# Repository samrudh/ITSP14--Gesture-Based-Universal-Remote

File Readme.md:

A summer project done in May-June 2014
| Gesture Based universal remote |

Description: It is a project aimed at 
implementing gesture based universal remote control of all the devices 
working with IR remote protocol.

Our wearable device first learns the IR codes, and mimic its functionality
when particular gesture is made.

Authors:
Ankit Patil,
Shubham Patil,
Sukhada Bakare

Mentor:
Samrudha Kelkar

Reference:
Arduino IR library
IRremote library for the Arduino.
For details on the library see the Wiki on github or the blog post http://arcfn.com/2009/08/multi-protocol-infrared-remote-library.html

Copyright 2009-2012 Ken Shirriff

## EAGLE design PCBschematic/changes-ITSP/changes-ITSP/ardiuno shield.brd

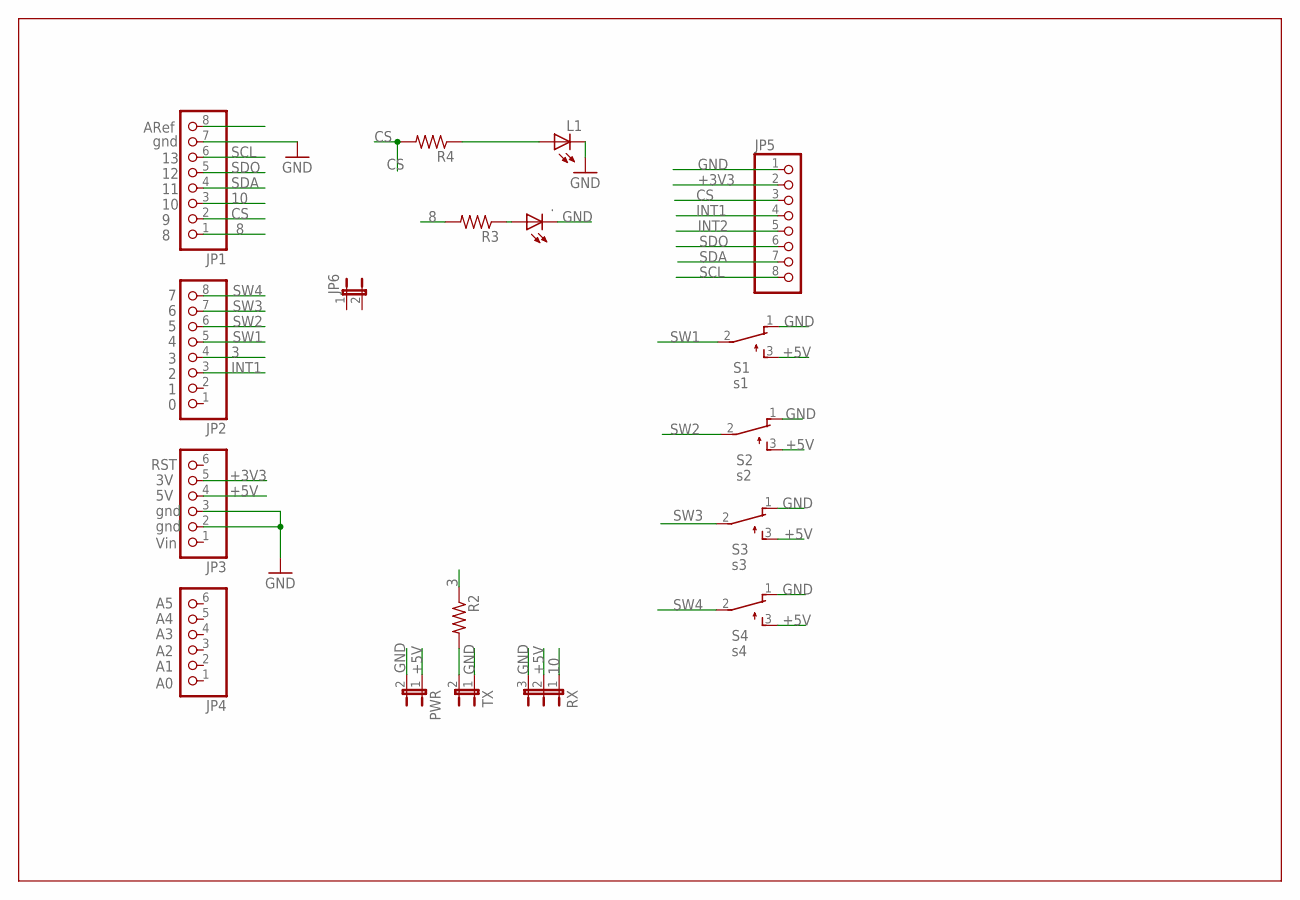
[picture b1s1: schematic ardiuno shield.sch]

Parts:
.: LED5MM
JP1, JP2, JP5: PINHD-1X8; 1X08
JP3, JP4: PINHD-1X6; 1X06
JP6: JP1E; JP1
L1: LED5MM
PWR: JP1E; JP1
R2, R3, R4: R-US_0207/10; 0207/10
RX: JP2E; JP2
S1: s1; TL3XPO
S2: s2; TL3XPO
S3: s3; TL3XPO
S4: s4; TL3XPO
TX: JP1E; JP1

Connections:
3: JP2.4, R2.1
8: JP1.1, R3.2
10: JP1.3, RX.1
+3V3: JP3.5, JP5.2
+5V: JP3.4, PWR.1, RX.2, S1.3 (S), S2.3 (S), S3.3 (S), S4.3 (S)
CS: JP1.2, JP5.3, R4.2
GND: ..K (C), JP1.7, JP3.2, JP3.3, JP5.1, L1.K (C), PWR.2, RX.3, S1.1 (O), S2.1 (O), S3.1 (O), S4.1 (O), TX.1
INT1: JP2.3, JP5.4
INT2: JP5.5
unnamed: L1.A, R4.1
unnamed: ..A, R3.1
unnamed: R2.2, TX.2
SCL: JP1.6, JP5.8
SDA: JP1.4, JP5.7
SDO: JP1.5, JP5.6
SW1: JP2.5, S1.2
SW2: JP2.6, S2.2
SW3: JP2.7, S3.2
SW4: JP2.8, S4.2

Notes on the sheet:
gnd
ARef
Vin
RST

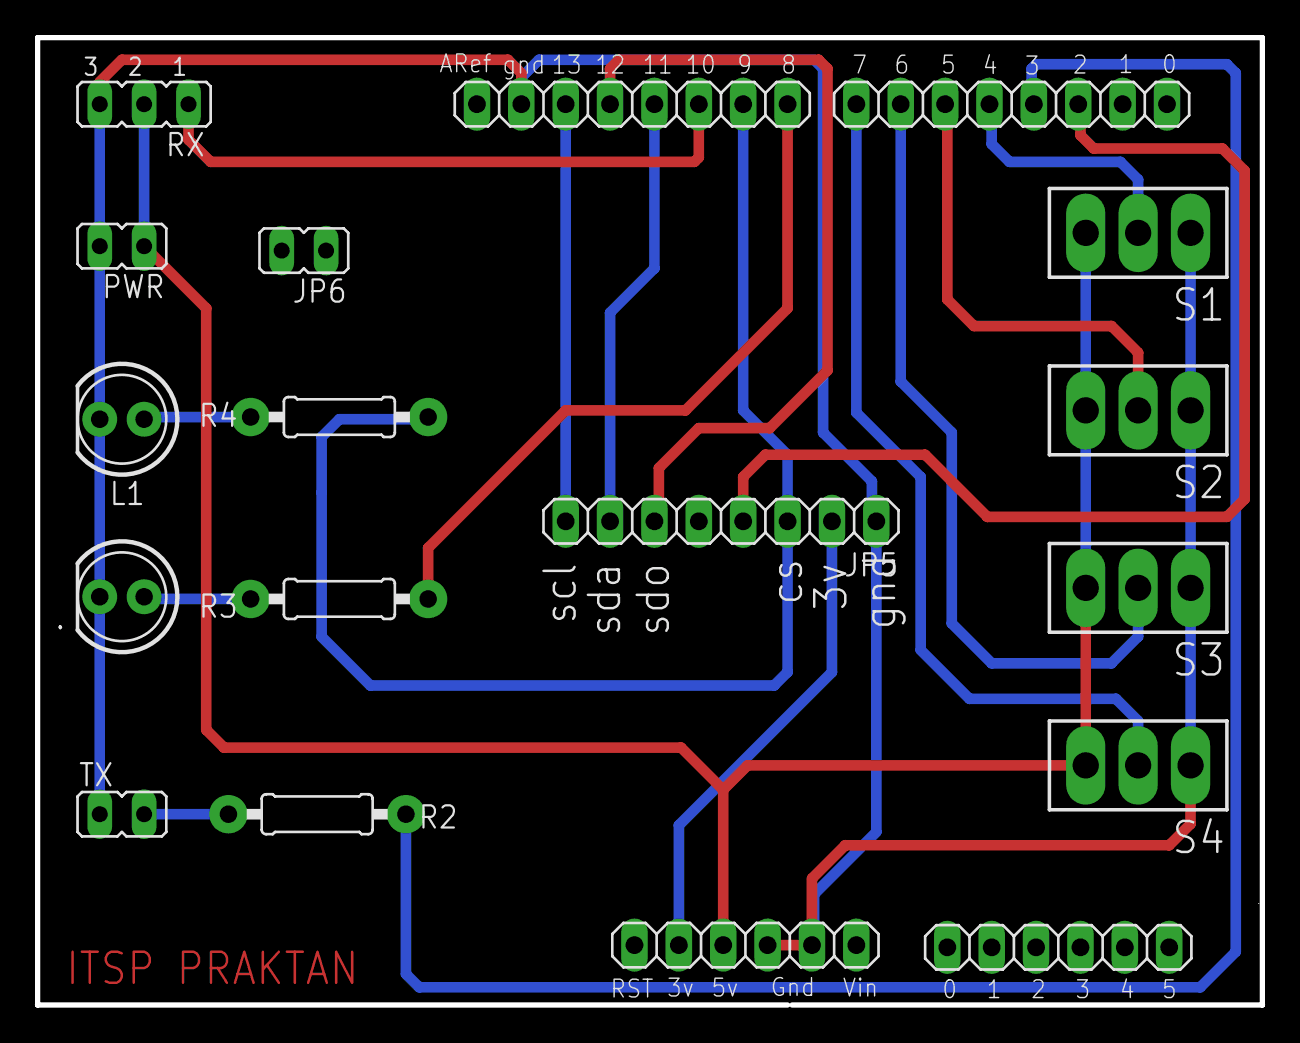
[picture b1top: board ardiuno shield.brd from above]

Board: 2 copper layers, 70.1 x 55.4 mm, 18 parts (0 on the bottom side), 18 nets.

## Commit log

2014-07-21 ITSP project
    summer 2014
2014-07-21 Revert "ITSP project"
    This reverts commit a9dd9a35778b8e19f8f417b2bbf21f2045968359.
2014-07-21 added Readme.txt
2014-07-21 add ppt2
2014-07-21 Change Readme
2014-07-21 add project
2014-07-21 mantor
2014-07-21 add description in readme
2014-07-21 PCBsch
2014-07-21 Revert "PCBsch"
    This reverts commit d2014356d91254ba64c02e43b214b1cf70fa032a.
2014-07-21 reeadme change
